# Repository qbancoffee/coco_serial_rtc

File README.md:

# coco_serial_rtc
An external Real Time Clock circuit (RTC) for the Tandy CoCo.

This is a realtime clock prototype for the Tandy CoCo. The board connects to the CoCo's bit banger serial port via a male DIN connector pigtail.
Whith the appropriate commands from the CoCo, one can get the date/time or one can set the date/time. The rest of the time it just sits in place and works as a serial passthrough so that you can still connect other serial devices to the CoCo. The other serial devices can connect to the onboard DIN connector. The board requires +5V DC and can be powered from the CoCo's joystick port or one can provide the voltage to a 2 pin terminal strip. The board also serves a passthrough when using the joystick port.

The board was designed using KiCAD 6 and the firmware was written in C and compiled with the [CCS C Compiler](https://www.ccsinfo.com/compilers.php).

## CoCo Serial RTC
- [Schematic](coco_serial_rtc_schematic.pdf)
- [Rendered Image](images/coco_serial_rtc_top.png)
- [Picture 1](images/coco_serial_rtc.jpg)
- [Picture 2](images/coco_serial_rtc_assembled_1.jpg)
- [Picture 3](images/coco_serial_rtc_assembled_2.jpg)
- [Picture 4](images/coco_serial_rtc_assembled_3.jpg)

## How it works
Add stuff here.

### Current status
- [x] Ordered
- [x] Assembled
- [x] Testing

The board is still in the prototype stage but so far things are looking good.

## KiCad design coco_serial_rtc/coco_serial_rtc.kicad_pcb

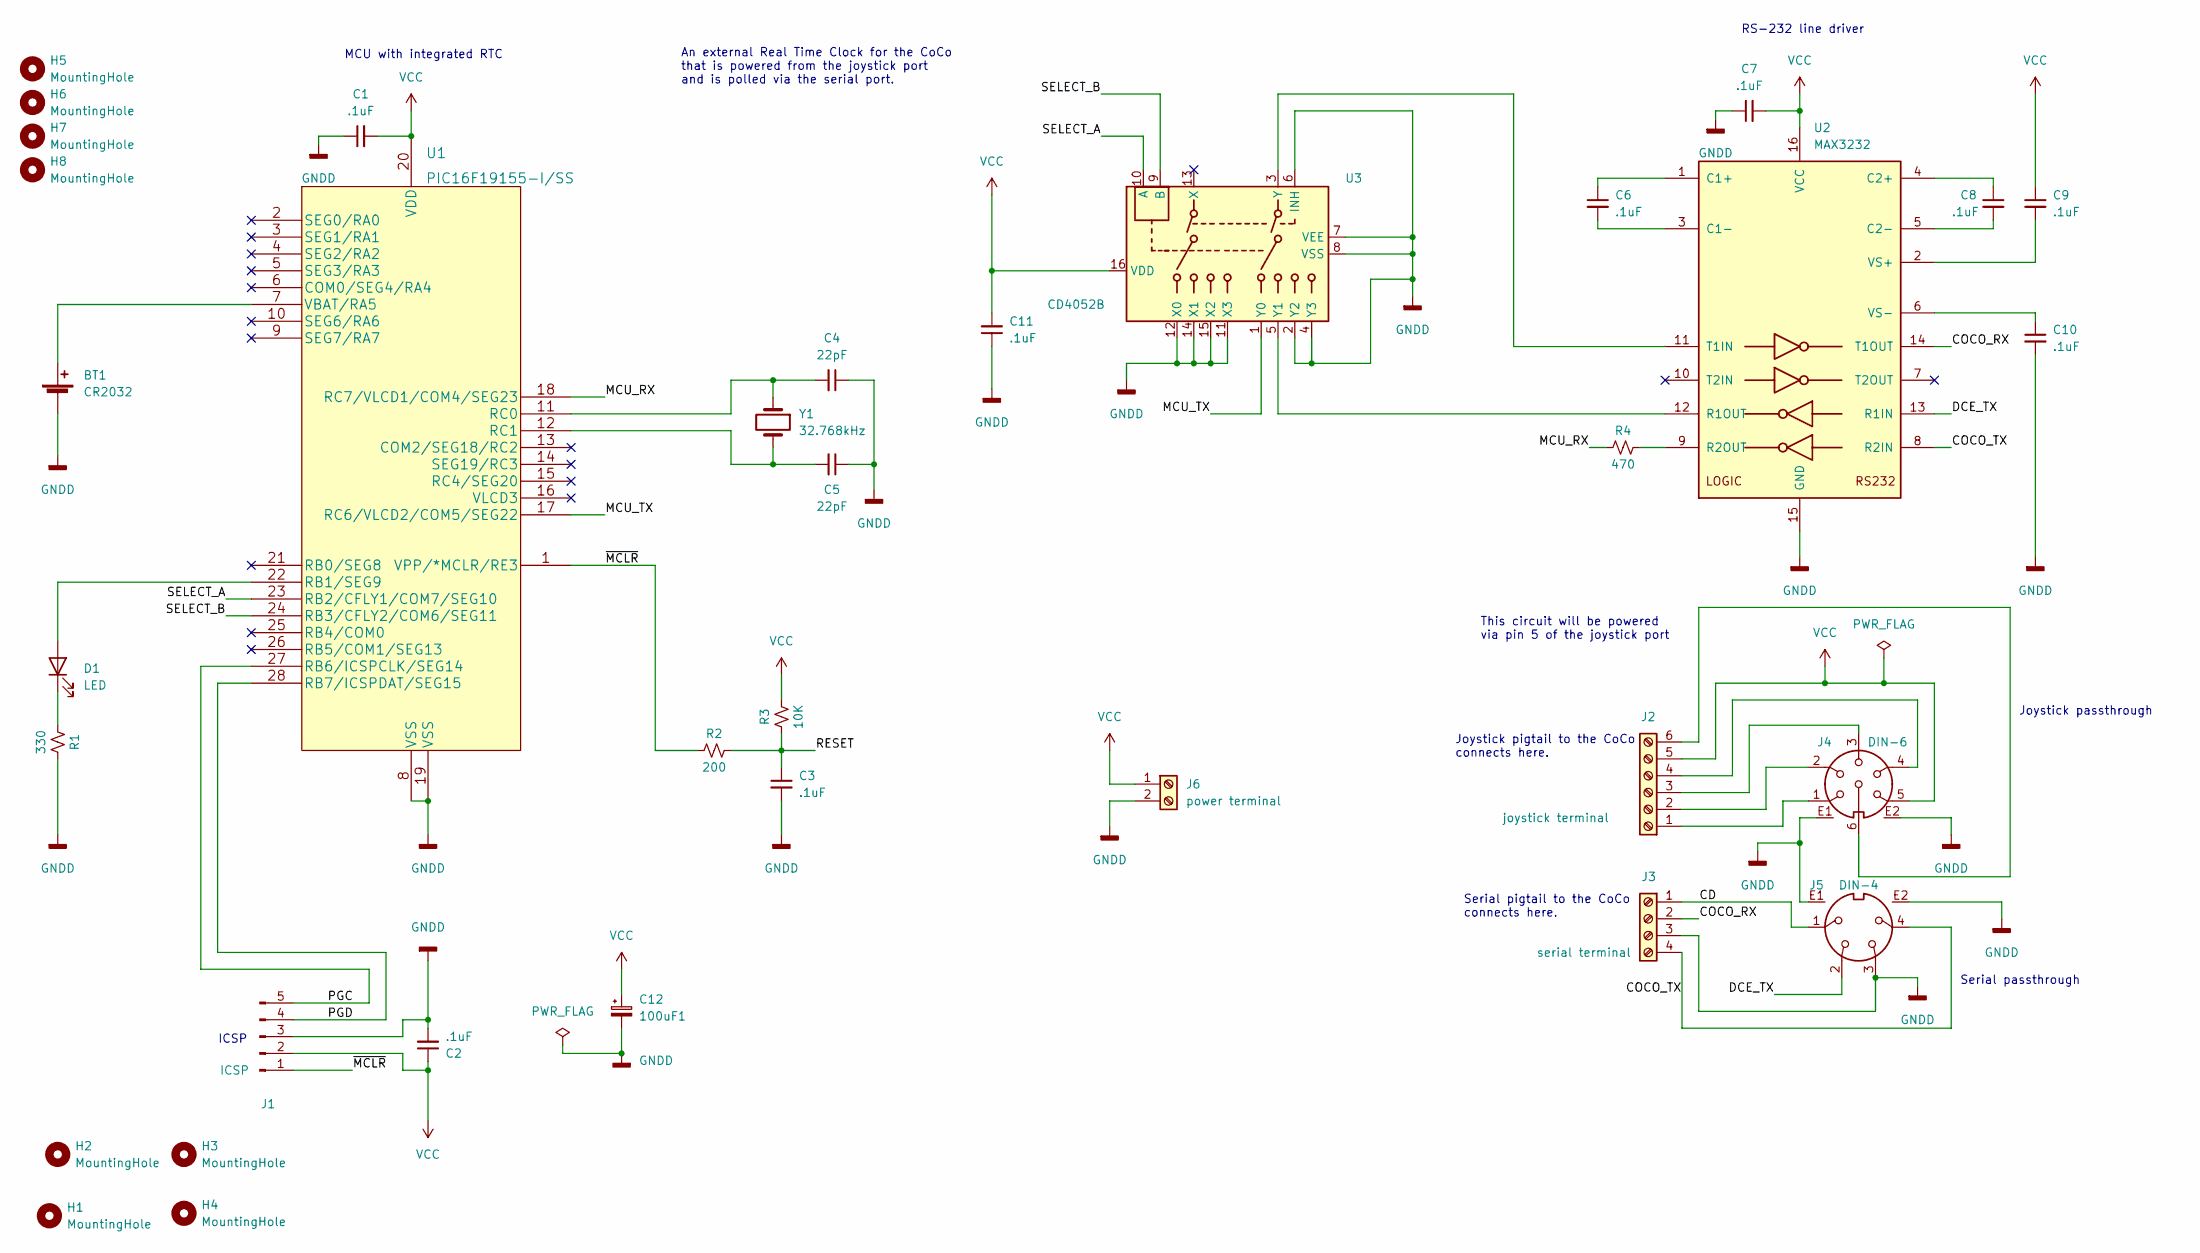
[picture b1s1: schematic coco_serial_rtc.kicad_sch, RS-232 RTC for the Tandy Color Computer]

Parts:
BT1: CR2032; BatteryHolder_Keystone_1058_1x2032; Manufacturer part# BS-06-B4AA015
C1, C2, C3, C6, C7, C8, C9, C10, C11: .1uF; C_0805_2012Metric_Pad1.18x1.45mm_HandSolder; Manufacturer part# CC0805KRX7R9BB104
C4, C5: 22pF; C_0805_2012Metric_Pad1.18x1.45mm_HandSolder; Manufacturer part# CL21C220JBANNNC
C12: 100uF1; CP_EIA-3528-21_Kemet-B_Pad1.50x2.35mm_HandSolder; Manufacturer part# TAJB107K006RNJ
D1: LED; LED_0805_2012Metric_Pad1.15x1.40mm_HandSolder; Manufacturer part# 17-21SUYC/TR8
H1, H2, H3, H4: MountingHole; MountingHole_4mm
H5, H6, H7, H8: MountingHole; MountingHole_3mm_Pad
J1: ICSP; PinHeader_1x05_P2.54mm_Vertical
J2: joystick terminal; TerminalBlock_Phoenix_MKDS-1,5-6_1x06_P5.00mm_Horizontal; Manufacturer part# 1935161
J3: serial terminal; TerminalBlock_Phoenix_MKDS-1,5-4_1x04_P5.00mm_Horizontal; Manufacturer part# 1935161
J4: DIN-6; CUI_SDS-60J; Manufacturer part# SDS-60J
J5: DIN-4; CUI_SDS-40J; Manufacturer part# SDS-40J
J6: power terminal; TerminalBlock_Phoenix_MKDS-1,5-2_1x02_P5.00mm_Horizontal; Manufacturer part# 1935161
R1: 330; R_0805_2012Metric_Pad1.20x1.40mm_HandSolder
R2: 200; R_0805_2012Metric_Pad1.20x1.40mm_HandSolder; Manufacturer part# 0805W8F2000T5E
R3: 10K; R_0805_2012Metric_Pad1.20x1.40mm_HandSolder; Manufacturer part# 0805W8F1002T5E
R4: 470; R_0805_2012Metric_Pad1.20x1.40mm_HandSolder; Manufacturer part# 0805W8F4700T5E
U1: PIC16F19155-I/SS; SSOP-28_5.3x10.2mm_P0.65mm; Manufacturer part# PIC16F19155-I/SS
U2: MAX3232; TSSOP-16-1EP_4.4x5mm_P0.65mm; Manufacturer part# MAX3232EUE+T
U3: CD4052B; SOIC-16_3.9x9.9mm_P1.27mm; Manufacturer part# CD4052BM96
Y1: 32.768kHz; Crystal_C26-LF_D2.1mm_L6.5mm_Horizontal; Manufacturer part# CFS-20632768DZBB

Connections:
/CD: J3.1, J5.1
/COCO_RX: J3.2, U2.14 (T1OUT)
/COCO_TX: J3.4, J5.4, U2.8 (R2IN)
/DCE_TX: J5.2, U2.13 (R1IN)
/MCU_RX: R4.1, U1.18 (RC7/VLCD1/COM4/SEG23)
/MCU_TX: U1.17 (RC6/VLCD2/COM5/SEG22), U3.1 (Y0)
/PGC: J1.5, U1.27 (RB6/ICSPCLK/SEG14)
/PGD: J1.4, U1.28 (RB7/ICSPDAT/SEG15)
/RESET: C3.1, R2.2, R3.1
/SELECT_A: U1.23 (RB2/CFLY1/COM7/SEG10), U3.10 (A)
/SELECT_B: U1.24 (RB3/CFLY2/COM6/SEG11), U3.9 (B)
/~MCLR: J1.1, R2.1, U1.1 (VPP/*MCLR/RE3)
GNDD: BT1.2 (-), C1.1, C2.2, C3.2, C4.1, C5.1, C7.1, C10.2, C11.1, C12.2, J1.3, J3.3, J4.E1, J4.E2, J5.3, J5.E1, J5.E2, J6.2, R1.2, U1.8 (VSS), U1.19 (VSS), U2.15 (GND), U3.2 (Y2), U3.4 (Y3), U3.6 (INH), U3.7 (VEE), U3.8 (VSS), U3.11 (X3), U3.12 (X0), U3.14 (X1), U3.15 (X2)
unnamed: BT1.1 (+), U1.7 (VBAT/RA5)
unnamed: C4.2, U1.11 (RC0), Y1.1
unnamed: C5.2, U1.12 (RC1), Y1.2
unnamed: C6.1, U2.1 (C1+)
unnamed: C6.2, U2.3 (C1-)
unnamed: C8.1, U2.4 (C2+)
unnamed: C8.2, U2.5 (C2-)
unnamed: C9.2, U2.2 (VS+)
unnamed: C10.1, U2.6 (VS-)
unnamed: D1.1 (K), R1.1
unnamed: D1.2 (A), U1.22 (RB1/SEG9)
unnamed: J2.1, J4.1
unnamed: J2.2, J4.2
unnamed: J2.3, J4.3
unnamed: J2.4, J4.4
unnamed: J2.6, J4.6
unnamed: R4.2, U2.9 (R2OUT)
unnamed: U2.11 (T1IN), U3.3 (Y)
unnamed: U2.12 (R1OUT), U3.5 (Y1)
VCC: C1.2, C2.1, C7.2, C9.1, C11.2, C12.1, J1.2, J2.5, J4.5, J6.1, R3.2, U1.20 (VDD), U2.16 (VCC), U3.16 (VDD)

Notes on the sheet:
RS-232 line driver
An external Real Time Clock for the CoCo that is powered from the joystick port and is polled via the serial port.
Joystick passthrough
MCU with integrated RTC
Joystick pigtail to the CoCo connects here.
This circuit will be powered via pin 5 of the joystick port
ICSP
Serial pigtail to the CoCo connects here.
Serial passthrough

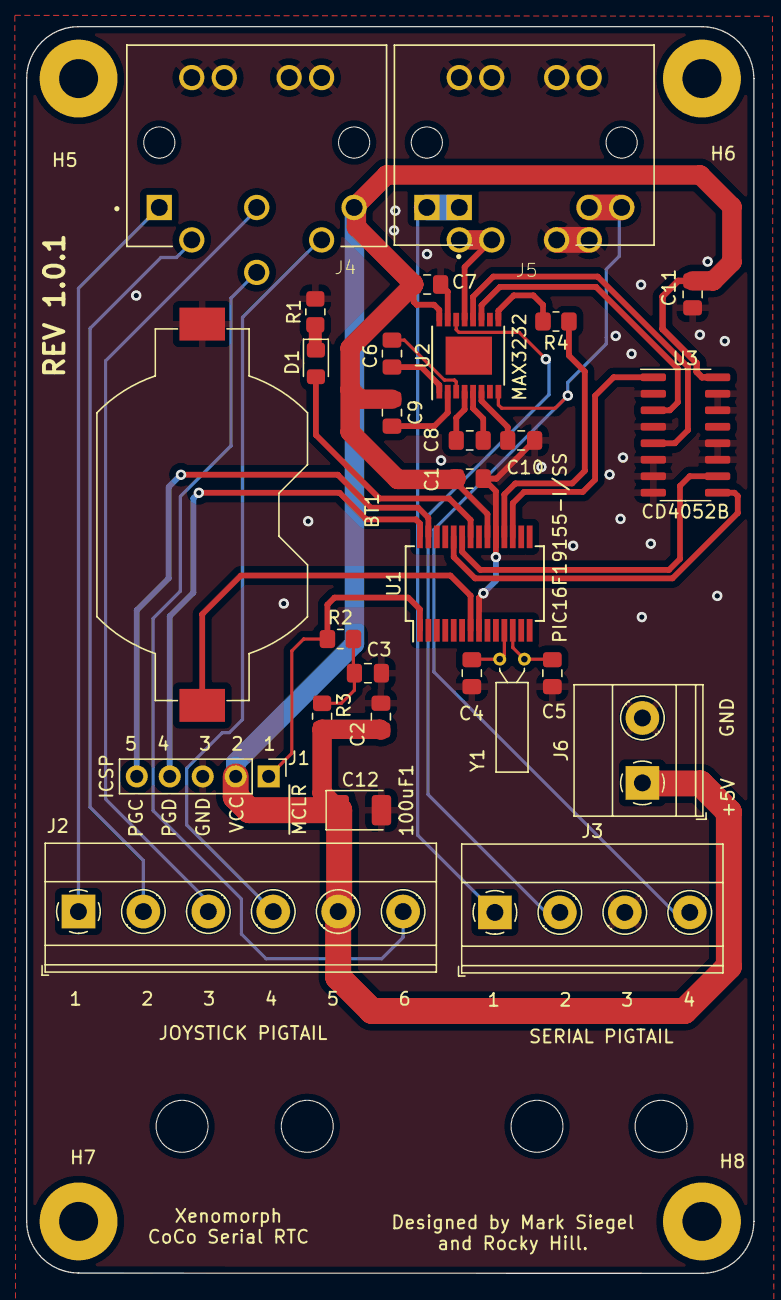
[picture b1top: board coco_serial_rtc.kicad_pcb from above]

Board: 2 copper layers, 56.0 x 96.0 mm, 36 parts (0 on the bottom side), 33 nets.

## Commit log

2023-06-17 added an image
2023-06-17 added more images
